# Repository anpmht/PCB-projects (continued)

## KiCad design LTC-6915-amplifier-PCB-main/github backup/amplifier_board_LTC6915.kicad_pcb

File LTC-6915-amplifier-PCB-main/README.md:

# LTC-6915-amplifier-PCB
single channel precision amplifier board with physical gain selection options. This amplifier board has gain selection options of 2,4,8,16,32,64,128,256,512,1024 and 4096. This board can be used for projects like load cell signal amplification, electrocardiogram signal amplification and various other small signal amplification applications. It uses lTC6915 instrumentation amplifier for signal amplification. it has input and output low pass filter for high prequency noise filter.

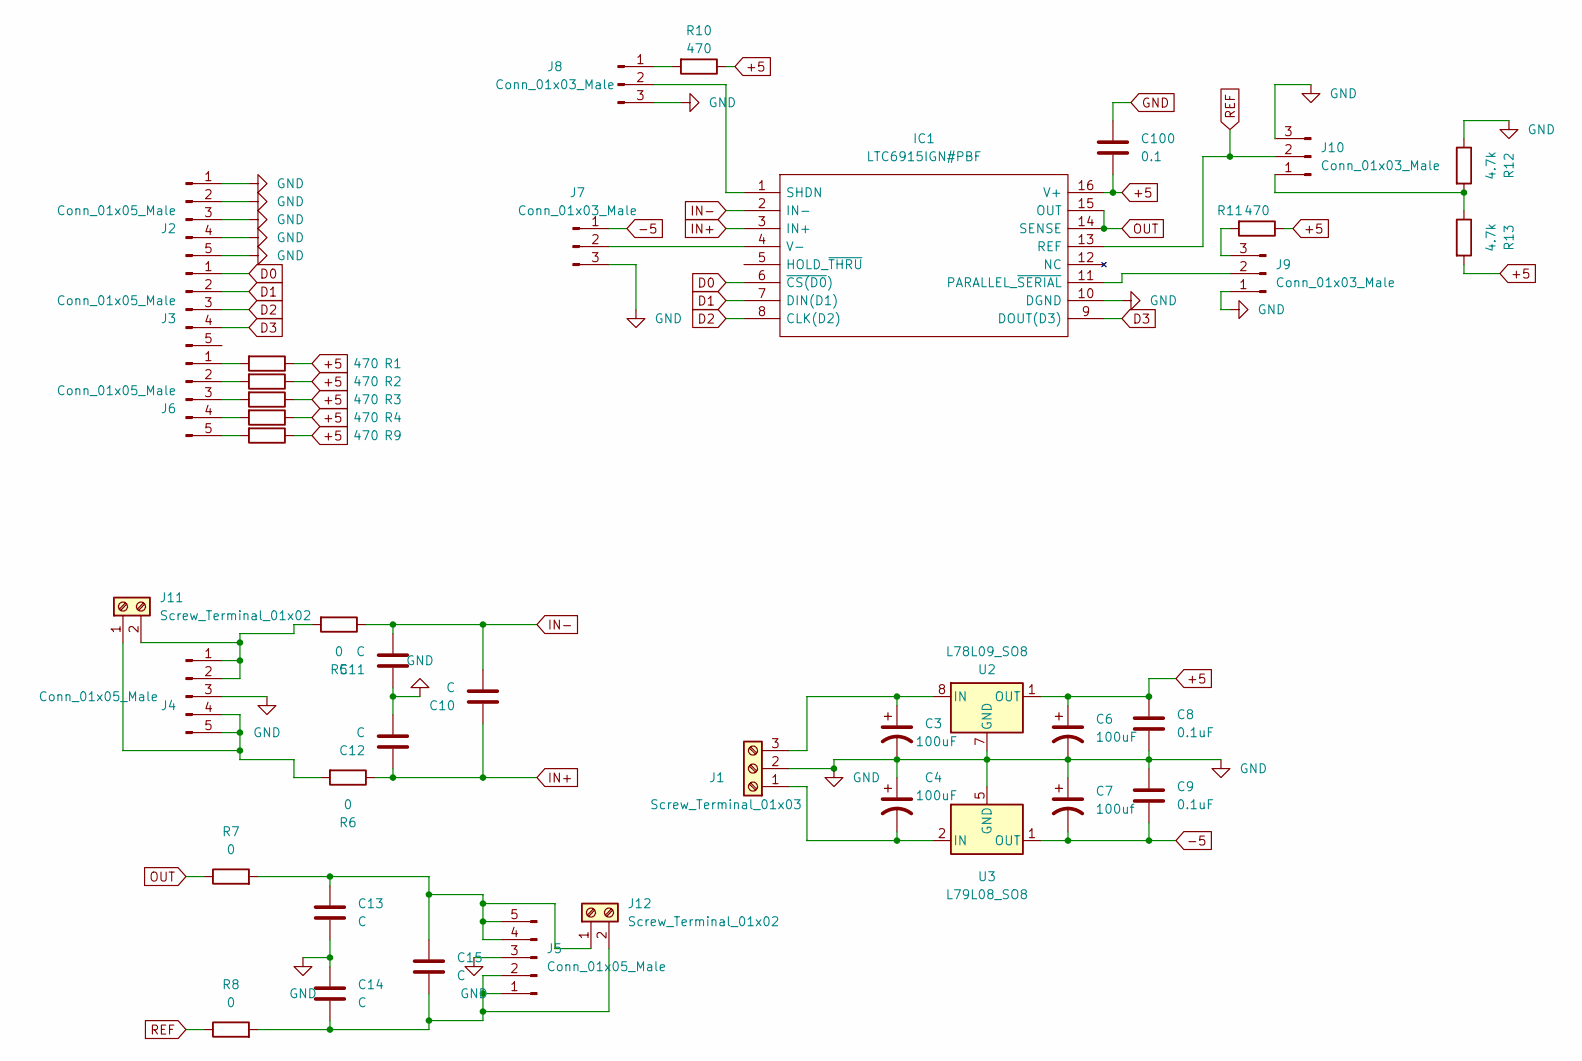
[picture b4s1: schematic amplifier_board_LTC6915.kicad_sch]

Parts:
C3, C4, C6: 100uF; CP_Radial_D6.3mm_P2.50mm
C7: 100uf; CP_Radial_D6.3mm_P2.50mm
C8, C9: 0.1uF; C_0603_1608Metric_Pad1.08x0.95mm_HandSolder
C10, C11, C12, C13, C14, C15: C; C_0603_1608Metric_Pad1.08x0.95mm_HandSolder
C100: 0.1; C_0603_1608Metric_Pad1.08x0.95mm_HandSolder
IC1: LTC6915IGN#PBF; SOP64P601X175-16N; Manufacturer_Part_Number LTC6915IGN#PBF; Mouser Part Number 584-LTC6915IGN#PBF
J1: Screw_Terminal_01x03; TerminalBlock_Philmore_TB133_1x03_P5.00mm_Horizontal
J2, J3, J4, J5, J6: Conn_01x05_Male; PinHeader_1x05_P2.54mm_Vertical
J7, J8, J9, J10: Conn_01x03_Male; PinHeader_1x03_P2.54mm_Vertical
J11, J12: Screw_Terminal_01x02; TerminalBlock_Philmore_TB132_1x02_P5.00mm_Horizontal
R1, R2, R3, R4, R9, R10, R11: 470; R_0603_1608Metric_Pad0.98x0.95mm_HandSolder
R5, R6, R7, R8: 0; R_0603_1608Metric_Pad0.98x0.95mm_HandSolder
R12, R13: 4.7k; R_0603_1608Metric_Pad0.98x0.95mm_HandSolder
U2: L78L09_SO8; SOIC-8_3.9x4.9mm_P1.27mm
U3: L79L08_SO8; SOIC-8_3.9x4.9mm_P1.27mm

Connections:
+5: C6.1, C8.1, C100.2, IC1.16 (V+), R1.1, R2.1, R3.1, R4.1, R9.1, R10.1, R11.1, R13.2, U2.1 (OUT); also elsewhere on the board
-5: C7.2, C9.2, J7.1, U3.1 (OUT)
D0: IC1.6 (~CS(D0)), J3.1
D1: IC1.7 (DIN(D1)), J3.2
D2: IC1.8 (CLK(D2)), J3.3
D3: IC1.9 (DOUT(D3)), J3.4
GND: C3.2, C4.1, C6.2, C7.1, C8.2, C9.1, C11.1, C12.2, C13.2, C14.1, IC1.10 (DGND), J1.2, J2.1, J2.2, J2.3, J2.4, J2.5, J4.3, J5.3, J7.3, J8.3, J9.1, J10.3, R12.1, U2.2 (GND), U2.3 (GND), U2.6 (GND), U2.7 (GND), U3.5 (GND); also elsewhere on the board
IN+: C10.1, C12.1, IC1.3 (IN+), R6.1
IN-: C10.2, C11.2, IC1.2 (IN-), R5.1
unnamed: C3.1, J1.3, U2.8 (IN)
unnamed: C4.2, J1.1, U3.2 (IN), U3.3 (IN), U3.6 (IN), U3.7 (IN)
unnamed: C13.1, C15.1, J5.4, J5.5, J12.1, R7.2
unnamed: C14.2, C15.2, J5.1, J5.2, J12.2, R8.2
unnamed: IC1.1 (SHDN), J8.2
unnamed: IC1.4 (V-), J7.2
unnamed: IC1.11 (PARALLEL_~SERIAL), J9.2
unnamed: J6.1, R1.2
unnamed: J6.2, R2.2
unnamed: J6.3, R3.2
unnamed: J6.4, R4.2
unnamed: J6.5, R9.2
unnamed: J8.1, R10.2
unnamed: J9.3, R11.2
unnamed: J10.1, R12.2, R13.1
unnamed: J4.4, J4.5, J11.1, R6.2
unnamed: J4.1, J4.2, J11.2, R5.2
OUT: IC1.14 (SENSE), IC1.15 (OUT), R7.1
REF: IC1.13 (REF), J10.2, R8.1

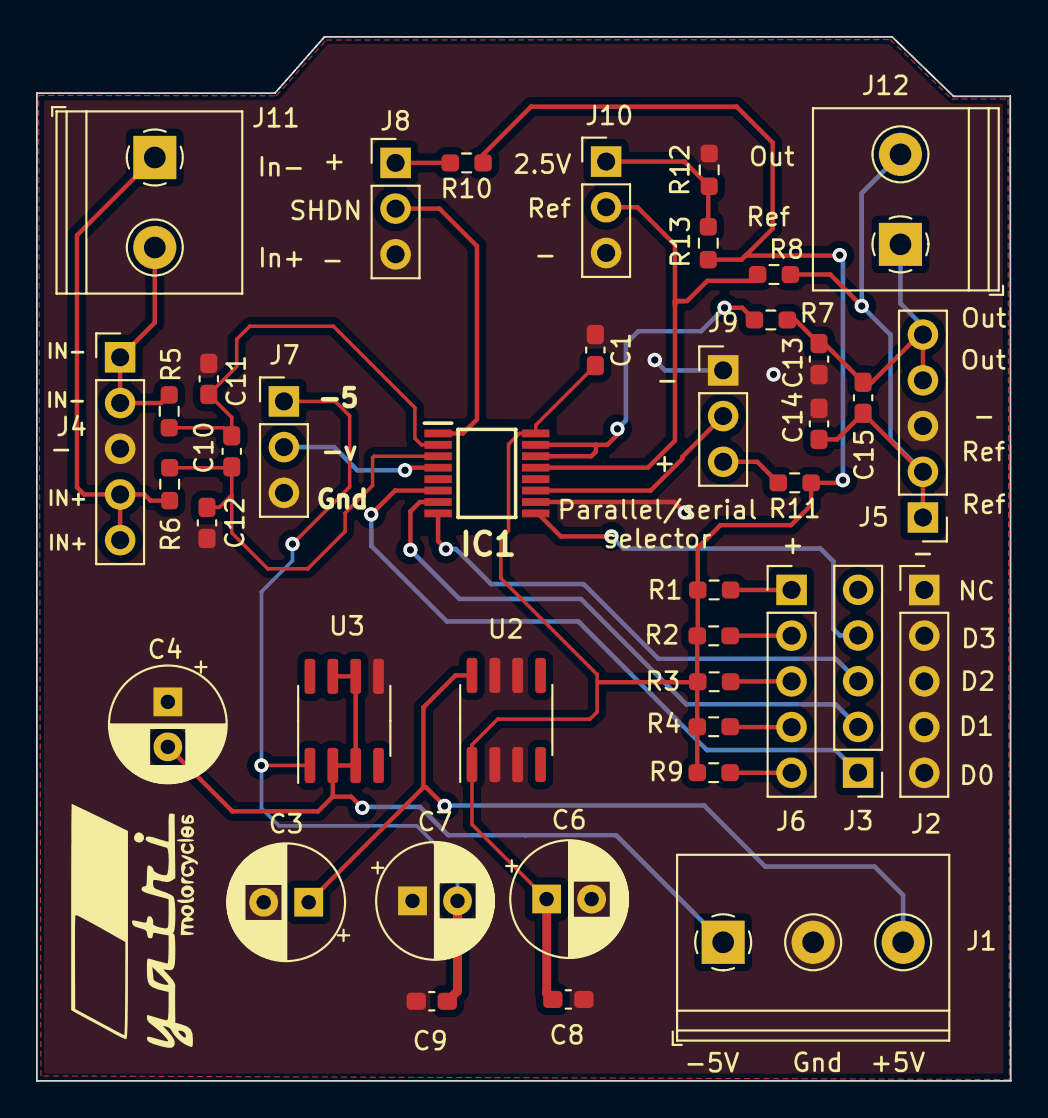
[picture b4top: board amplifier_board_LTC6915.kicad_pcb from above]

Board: 2 copper layers, 54.1 x 58.0 mm, 41 parts (0 on the bottom side), 28 nets.

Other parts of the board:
C1: 0.1; C_0603_1608Metric_Pad1.08x0.95mm_HandSolder

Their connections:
+5: C1.2; also elsewhere on the board
GND: C1.1; also elsewhere on the board
